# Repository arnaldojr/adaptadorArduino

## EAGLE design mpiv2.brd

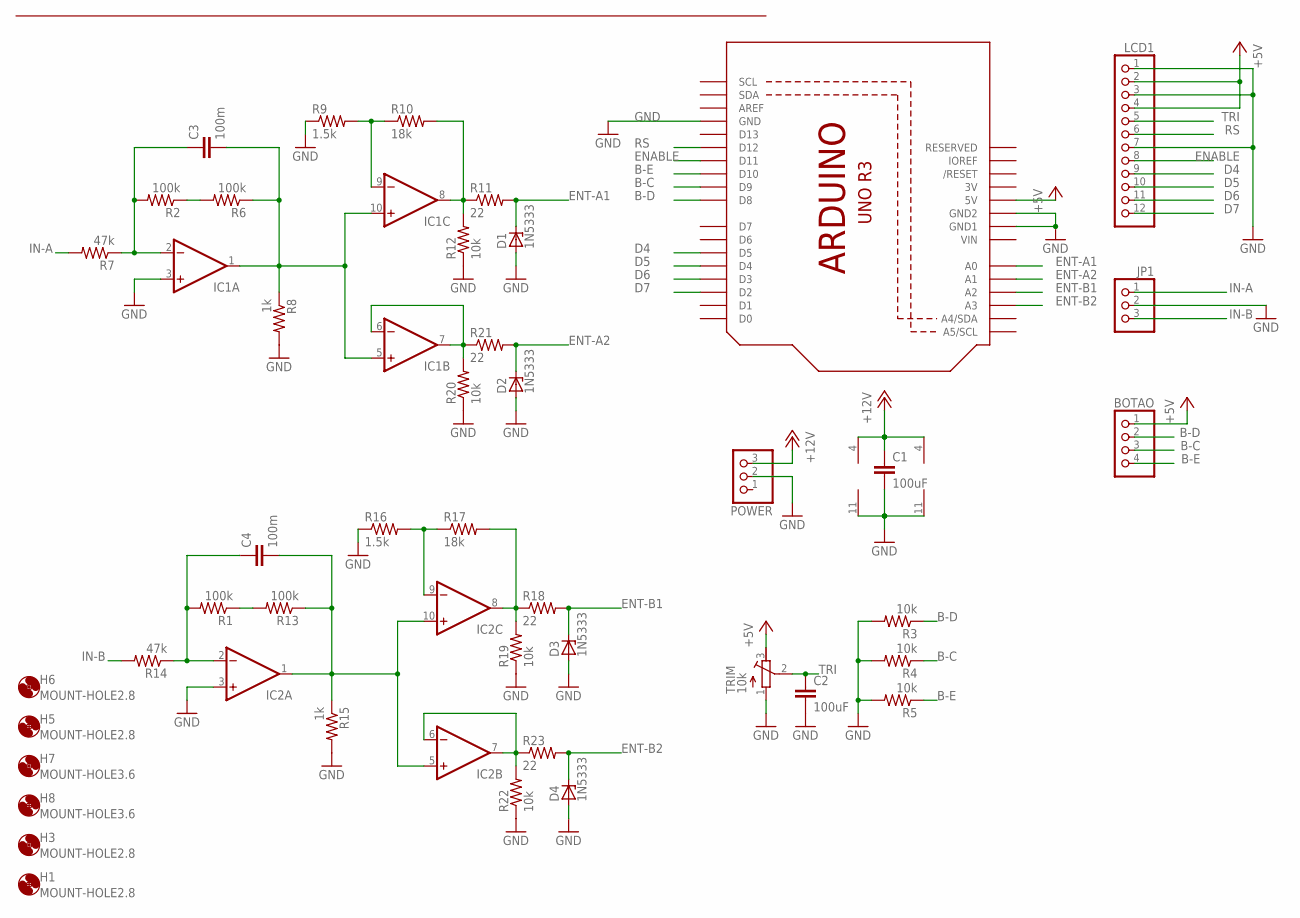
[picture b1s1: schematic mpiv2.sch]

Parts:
BOTAO: HEADER-1X4; 1X04_OVAL
C1, C2: 100uF; C050-035X075
C3, C4: 100m; C075-032X103
D1, D2, D3, D4: 1N5333; C1702-15
H1, H3, H5, H6: MOUNT-HOLE2.8; 2,8
H7, H8: MOUNT-HOLE3.6; 3,6
IC1, IC2: 4AMP_P4+11N; DIL14
JP1: PINHD-1X3; 1X03
LCD1: PINHD-1X12; 1X12
POWER: HEADER-1X3; 1X03_OVAL
R1, R2, R6, R13: 100k; 0207/10
R3, R4, R5, R12, R19, R20, R22: 10k; 0207/10
R7, R14: 47k; 0207/10
R8, R15: 1k; 0207/10
R9, R16: 1.5k; 0207/10
R10, R17: 18k; 0207/10
R11, R18, R21, R23: 22; 0207/10
TRIM: 10k; RTRIM74W
U1: ARDUINOR3-BPLACE

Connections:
3V: U1.3V
+5V: BOTAO.1, LCD1.2, LCD1.4, TRIM.3 (A), U1.5V
+12V: C1.1, IC1.4 (V+), IC2.4 (V+), POWER.3
B-C: BOTAO.3, R4.1, U1.D9
B-D: BOTAO.2, R3.1, U1.D8
B-E: BOTAO.4, R5.1, U1.D10
D4: LCD1.9, U1.D5
D5: LCD1.10, U1.D4
D6: LCD1.11, U1.D3
D7: LCD1.12, U1.D2
ENABLE: LCD1.8, U1.D11
ENT-A1: D1.C, R11.2, U1.A0
ENT-A2: D2.C, R21.2, U1.A1
ENT-B1: D3.C, R18.2, U1.A2
ENT-B2: D4.C, R23.2, U1.A3
GND: C1.2, C2.2, D1.A, D2.A, D3.A, D4.A, IC1.3 (+IN), IC1.11 (V-), IC2.3 (+IN), IC2.11 (V-), JP1.2, LCD1.1, LCD1.3, LCD1.7, POWER.2, R3.2, R4.2, R5.2, R8.2, R9.1, R12.1, R15.2, R16.1, R19.1, R20.1, R22.1, TRIM.1 (E), U1.GND, U1.GND1, U1.GND2
IN-A: JP1.1, R7.2
IN-B: JP1.3, R14.2
unnamed: C4.1, IC2.2 (-IN), R1.2, R14.1
unnamed: C3.1, IC1.2 (-IN), R2.2, R7.1
unnamed: R2.1, R6.2
unnamed: C3.2, IC1.1 (OUT), IC1.5 (+IN), IC1.10 (+IN), R6.1, R8.1
unnamed: IC1.9 (-IN), R9.2, R10.1
unnamed: IC1.8 (OUT), R10.2, R11.1, R12.2
unnamed: IC1.6 (-IN), IC1.7 (OUT), R20.2, R21.1
unnamed: R1.1, R13.2
unnamed: C4.2, IC2.1 (OUT), IC2.5 (+IN), IC2.10 (+IN), R13.1, R15.1
unnamed: IC2.9 (-IN), R16.2, R17.1
unnamed: IC2.8 (OUT), R17.2, R18.1, R19.2
unnamed: IC2.6 (-IN), IC2.7 (OUT), R22.2, R23.1
RS: LCD1.6, U1.D12
TRI: C2.1, LCD1.5, TRIM.2 (S)
VIN: U1.VIN

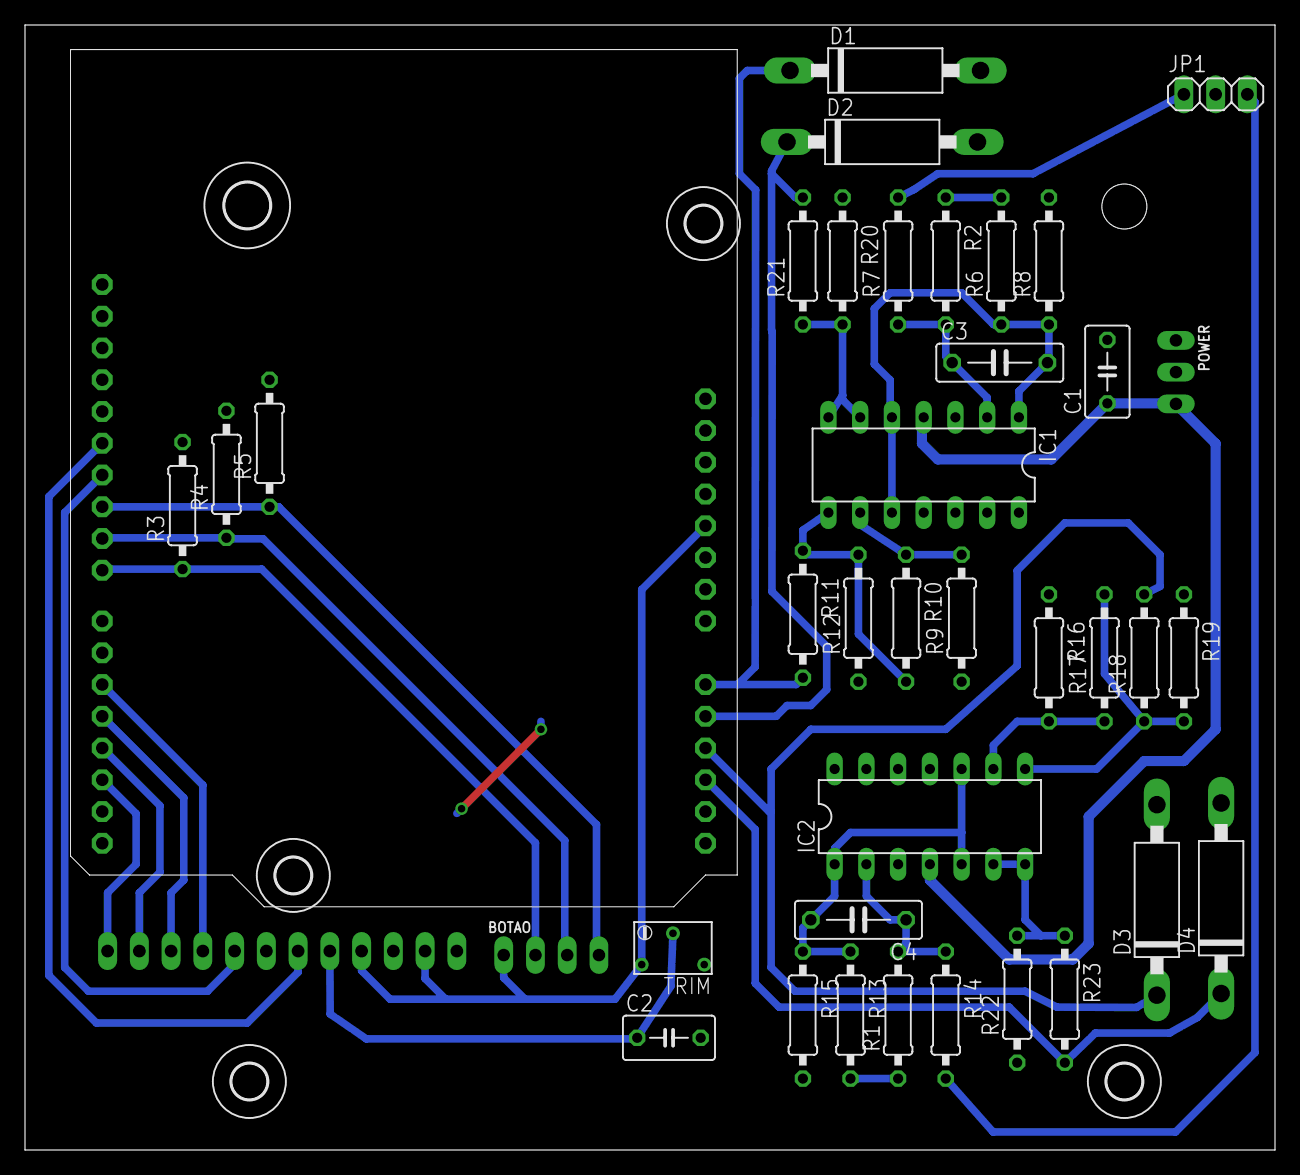
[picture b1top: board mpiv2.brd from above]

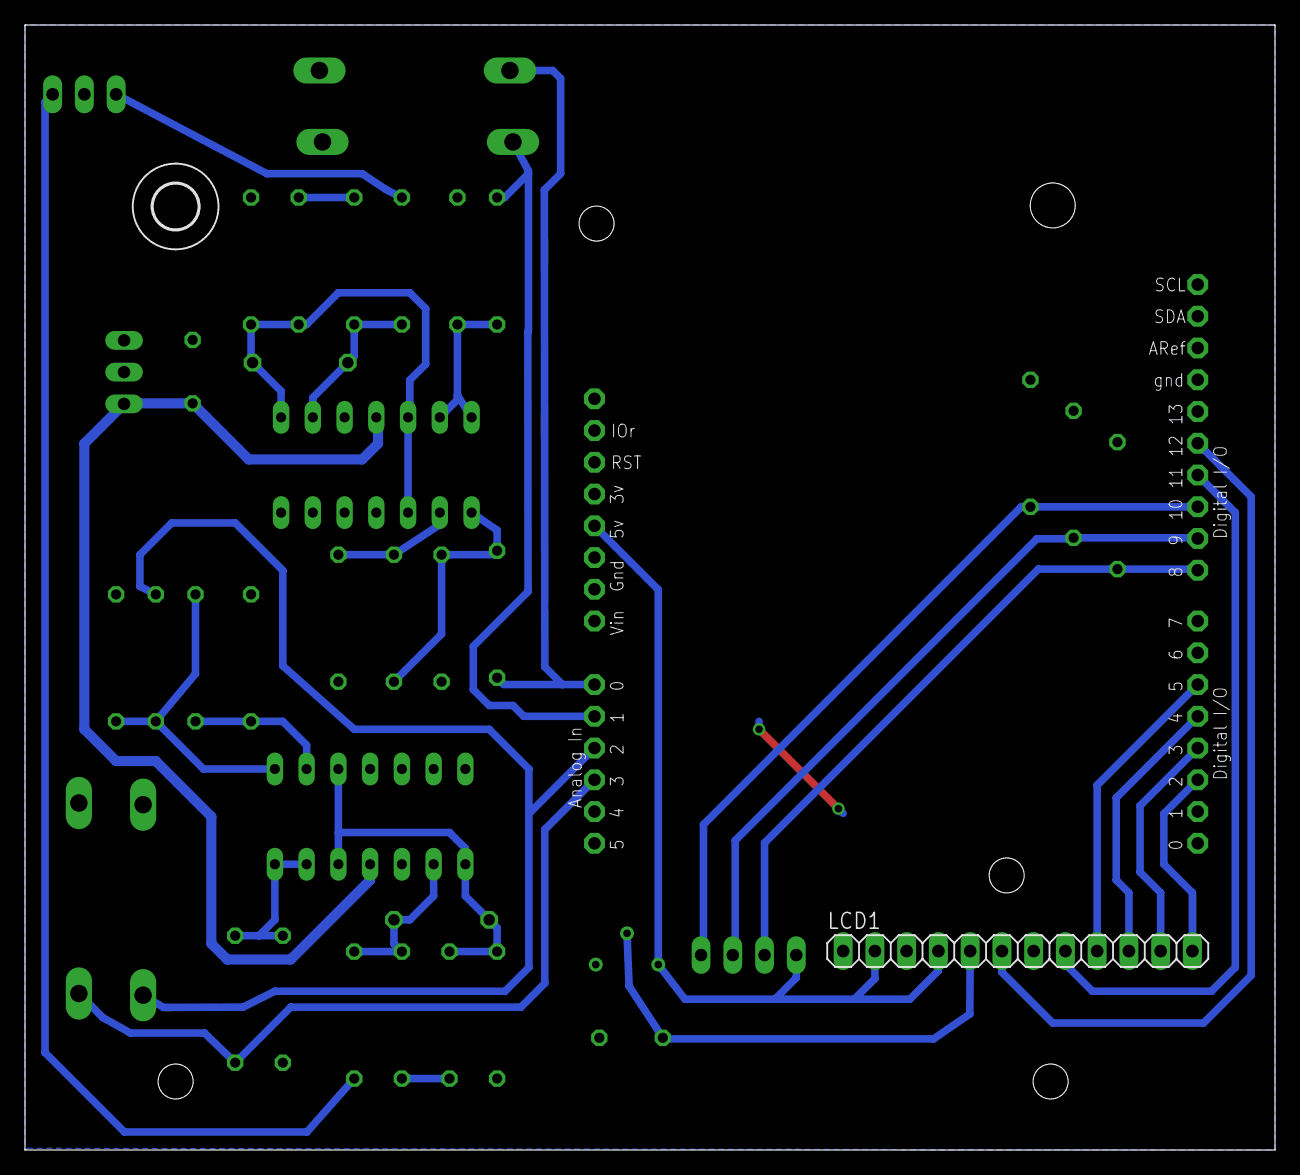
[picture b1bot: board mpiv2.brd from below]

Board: 2 copper layers, 100.0 x 90.0 mm, 45 parts (3 on the bottom side), 31 nets.

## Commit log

2018-11-02 init commit
